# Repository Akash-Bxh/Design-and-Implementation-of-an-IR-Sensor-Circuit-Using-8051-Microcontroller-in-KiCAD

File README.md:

# IR Sensor Using 8051 Micorcontroller
This IR sensor circuit uses an 8051 microcontroller to process input from a TSOP1738 IR receiver, detecting modulated IR signals and controlling LEDs as indicators. It can be used for applications like remote control systems, obstacle detection, and proximity sensors.
## Circuit Overview:
An 8051 microcontroller is used to process the input from an IR sensor (TSOP1738) and control LED indicators.
The TSOP1738 detects modulated IR signals (typically 38 kHz) and sends an output signal to the microcontroller.
The microcontroller processes the signal and triggers LEDs to indicate detection.
## Components and Functions:
* TSOP1738 (IR Receiver):
Detects IR signals.
Sends output to the microcontroller.
* 8051 Microcontroller:
Processes IR sensor output.
Controls LEDs and other peripherals.
* Crystal Oscillator (Y1):
Provides clock signal for the microcontroller.
* Push Button (SW1):
Used for manual input to trigger/reset functions.
* Resistor Network (RN1):
Limits current to protect microcontroller and LEDs.
LEDs (D1, D2, D3):
Visual indicators showing the detection of IR signals.
* Decoupling Capacitors (C1, C2, C3):
Filter noise from the power supply.
## Working:
* The IR sensor detects an IR signal and outputs a signal to the microcontroller.
* The 8051 microcontroller processes the input and turns on the corresponding LEDs.
* The Push Button allows manual triggering of the circuit.
## Applications:
* IR remote control systems.
* Obstacle detection and proximity sensors.

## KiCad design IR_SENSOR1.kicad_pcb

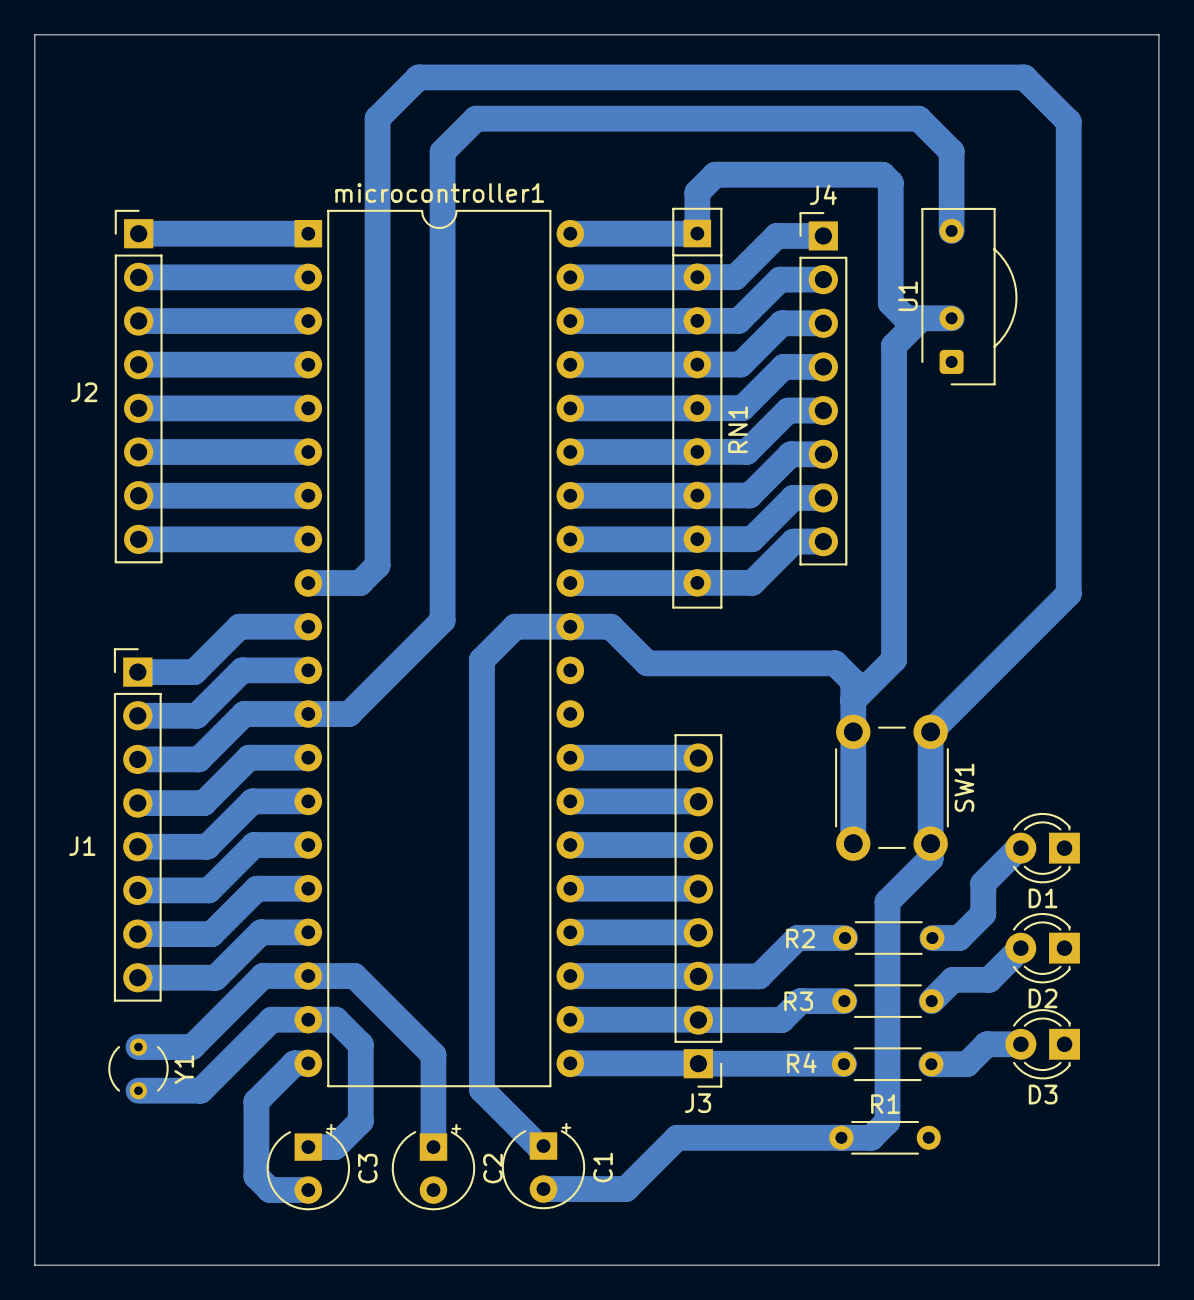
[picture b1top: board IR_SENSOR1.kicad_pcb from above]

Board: 2 copper layers, 65.4 x 71.6 mm, 19 parts (0 on the bottom side), 40 nets.

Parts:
C1, C2, C3: C_Small; CP_Radial_Tantal_D4.5mm_P2.50mm
D1, D2, D3: LED; LED_D3.0mm
J1, J2, J3, J4: Conn_01x08; PinHeader_1x08_P2.54mm_Vertical
R1, R2, R3, R4: R_Small_US; R_Axial_DIN0204_L3.6mm_D1.6mm_P5.08mm_Horizontal
RN1: R_Network08; R_Array_SIP9
SW1: SW_MEC_5E; SW_PUSH_6mm
U1: TSOP17xx; Vishay_CAST-3Pin
Y1: Crystal; Crystal_AT310_D3.0mm_L10.0mm_Vertical
microcontroller1: 8051; DIP-40_W15.24mm

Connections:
+5V: C1.1, RN1.1 (common), SW1.2, U1.2 (Vs), microcontroller1.31 (EAVP), microcontroller1.40 (VCC)
GND: C2.2, C3.2, D1.1 (K), D2.1 (K), D3.1 (K), R1.2, U1.1 (GND), microcontroller1.20 (GND)
unnamed: D1.2 (A), R2.2
unnamed: D2.2 (A), R3.2
unnamed: D3.2 (A), R4.2
unnamed: J1.1, microcontroller1.10 (RXD)
unnamed: J1.2, microcontroller1.11 (TXD)
unnamed: J1.3, U1.3 (OUT), microcontroller1.12 (INT0)
unnamed: J1.4, microcontroller1.13 (INT1)
unnamed: J1.5, microcontroller1.14 (T0)
unnamed: J1.6, microcontroller1.15 (T1)
unnamed: J1.7, microcontroller1.16 (WR)
unnamed: J1.8, microcontroller1.17 (RD)
unnamed: J2.1, microcontroller1.1 (P10)
unnamed: J2.2, microcontroller1.2 (P11)
unnamed: J2.3, microcontroller1.3 (P12)
unnamed: J2.4, microcontroller1.4 (P13)
unnamed: J2.5, microcontroller1.5 (P14)
unnamed: J2.6, microcontroller1.6 (P15)
unnamed: J2.7, microcontroller1.7 (P16)
unnamed: J2.8, microcontroller1.8 (P17)
unnamed: J3.1, R4.1, microcontroller1.21 (P20)
unnamed: J3.2, R3.1, microcontroller1.22 (P21)
unnamed: J3.3, R2.1, microcontroller1.23 (P22)
unnamed: J3.4, microcontroller1.24 (P23)
unnamed: J3.5, microcontroller1.25 (P24)
unnamed: J3.6, microcontroller1.26 (P25)
unnamed: J3.7, microcontroller1.27 (P26)
unnamed: J3.8, microcontroller1.28 (P27)
unnamed: J4.1, RN1.2 (R1), microcontroller1.39 (P00)
unnamed: J4.2, RN1.3 (R2), microcontroller1.38 (P01)
unnamed: J4.3, RN1.4 (R3), microcontroller1.37 (P02)
unnamed: J4.4, RN1.5 (R4), microcontroller1.36 (P03)
unnamed: J4.5, RN1.6 (R5), microcontroller1.35 (P04)
unnamed: J4.6, RN1.7 (R6), microcontroller1.34 (P05)
unnamed: J4.7, RN1.8 (R7), microcontroller1.33 (P06)
unnamed: J4.8, RN1.9 (R8), microcontroller1.32 (P07)
unnamed: C1.2, R1.1, SW1.1, microcontroller1.9 (RESET)
unnamed: C3.1, Y1.2, microcontroller1.19 (X1)
unnamed: C2.1, Y1.1, microcontroller1.18 (X2)
